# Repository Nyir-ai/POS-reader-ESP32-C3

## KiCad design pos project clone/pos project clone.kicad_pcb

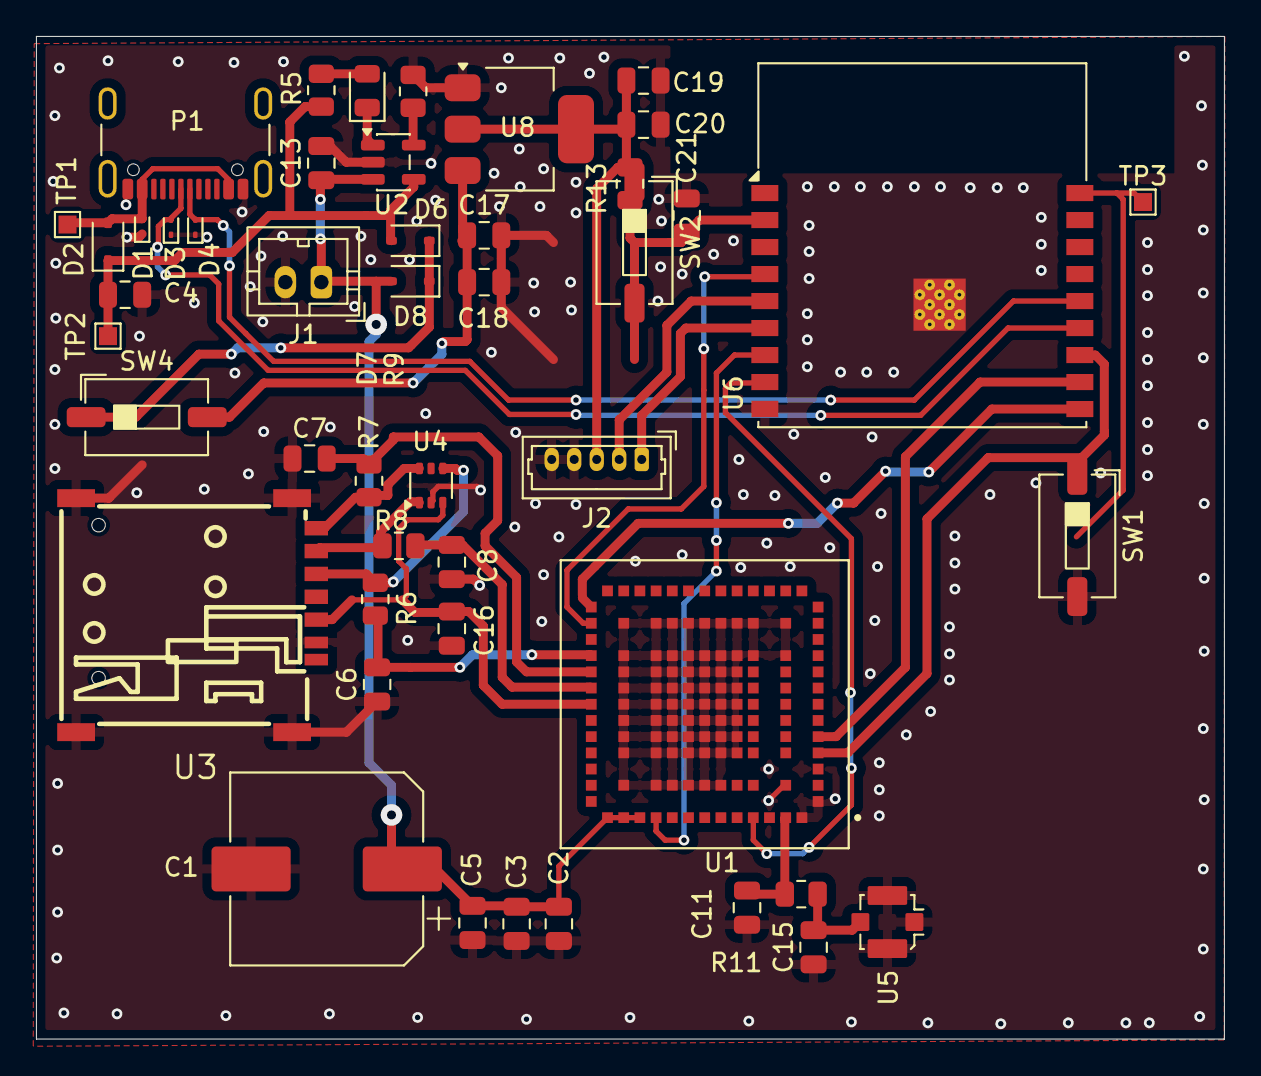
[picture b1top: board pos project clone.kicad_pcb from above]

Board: 2 copper layers, 66.0 x 55.7 mm, 47 parts (0 on the bottom side), 31 nets.

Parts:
C1: 330uF; CP_Elec_10x12.5
C2, C3: 100uF; C_0805_2012Metric
C4, C17, C18: 4.7uF; C_0805_2012Metric
C5: 1uF; C_0805_2012Metric
C6, C7, C8: 33P; C_0805_2012Metric
C11, C15: NC; C_0805_2012Metric
C13, C19, C20, C21: 100nF; C_0805_2012Metric
C16: 104; C_0805_2012Metric
D1, D3, D4: ESD9B3.3ST5G; D_SOD-923
D2: 1N5819WS; D_SOD-323
D6, D8: BAT60A; D_SOD-323
D7: LED; LED_0805_2012Metric
J1: JST_2mm_LiPo; TE_440054-2_1x02_P2.00mm_Vertical
J2: Conn_01x05_Socket; Molex_PicoBlade_53047-0510_1x05_P1.25mm_Vertical
P1: USB_C_Plug_USB2.0; USB_C_Receptacle_GCT_USB4105-xx-A_16P_TopMnt_Horizontal
R5, R9: R_US; R_0805_2012Metric
R6, R7, R8, R11: 22R; R_0805_2012Metric
R13: 10k; R_0805_2012Metric
SW1, SW2: SW_Push; SW_DIP_SPSTx01_Slide_6.7x4.1mm_W6.73mm_P2.54mm_LowProfile_J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
SW4: SW_SPST; SW_DIP_SPSTx01_Slide_6.7x4.1mm_W6.73mm_P2.54mm_LowProfile_J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
TP1: VBUS; TestPoint_Pad_1.0x1.0mm
TP2: VUSB; TestPoint_Pad_1.0x1.0mm
TP3: Test_point; TestPoint_Pad_1.0x1.0mm
U1: LEXI-R10801D-00B; XCVR_LEXI-R10801D-00B
U2: MCP73831-2-OT; SOT-23-5
U3: SMN-303; SIM-SMD_SMN-303
U4: SMF05C; SOT-363_SC-70-6
U5: GSM_ANT; U.FL_Molex_MCRF_73412-0110_Vertical
U6: ESP32-C3-WROOM-02
U8: SGM2212-3.3; SOT-223

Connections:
/ANT_DET: U1.49 (ANT_DET), U6.8 (IO9)
/CLK EN: R7.2, U3.3 (CLK), U4.6 (K5)
/DATA: J2.2 (DATA), U6.5 (IO6)
/DATA EN: R8.2, U3.7 (I/O), U4.1 (K1)
/ESP0/STAT: SW1.1, TP3.1, U6.18 (IO0)
/GPIO18: D3.2 (A2), P1.A7 (D-), U6.13 (IO18)
/GPIO19: D4.2 (A2), P1.A6 (D+), U6.14 (IO19)
/Main ANT: C11.2, R11.1, U1.51 (ANT)
/PWR_ON: U1.27 (~PWR_ON), U6.10 (IO10)
/RESET: U1.28 (~RESET), U6.4 (IO5)
/RST EN: R6.2, U3.2 (RST), U4.4 (K3)
/RXD: U1.4 (~RXD), U6.12 (IO21/TXD)
/SIM1 CLK: C7.2, R7.1, U1.31 (SIM_CLK)
/SIM1 DATA: C8.2, R8.1, U1.32 (SIM_IO)
/SIM1 RST: C6.2, R6.1, U1.30 (SIM_RST)
/SIM1 VCC: C16.1, U1.33 (VSIM), U3.1 (VCC), U4.3 (K2)
/STROBE: J2.1 (STROBE), U6.6 (IO7)
/TXD: U1.5 (~TXD), U6.11 (IO20/RXD)
/VCC_3V3: C19.1, C20.1, J2.3 (VDD), R13.1, U8.2 (VOUT), U8.4 (VOUT)
/V_INT: U1.43 (V_INT), U6.7 (IO8)
GND: C1.2, C2.2, C3.2, C4.2, C5.2, C6.1, C7.1, C8.1, C11.1, C13.2, C15.1, C16.2, C17.2, C18.2, C19.2, C20.2, C21.2, D1.1 (A1), D3.1 (A1), D4.1 (A1), J1.2, J2.4 (GND), J2.5 (CASE), P1.A1 (GND), P1.A12 (GND), P1.B1 (GND), P1.B12 (GND), R9.2, SW1.2, SW2.2, U1.1 (GND_1), U1.3 (GND_1), U1.50 (GND_1), U1.52 (GND_1), U1.53 (GND_1), U1.56 (GND_1), U1.57 (GND_1), U1.58 (GND_1), U1.59 (GND_1), U1.60 (GND_1), U1.61 (GND_1), U1.64 (GND_1), U1.65 (GND_1), U1.66 (GND_1), U1.67 (GND_1), U1.68 (GND_1), U1.69 (GND_1), U1.70 (GND_1), U1.73 (GND_1), U1.74 (GND_1), U1.75 (GND_1), U1.76 (GND_1), U1.77 (GND_1), U1.78 (GND_1), U1.79 (GND_1), U1.82 (GND_1), U1.83 (GND_1), U1.84 (GND_1), U1.85 (GND_1), U1.86 (GND_1), U1.87 (GND_1), U1.88 (GND_1), U1.91 (GND_1), U1.92 (GND_1), U1.93 (GND_1), U1.94 (GND_1), U1.95 (GND_2), U1.96 (GND_2), U1.97 (GND_2), U1.100 (GND_2), U1.101 (GND_2), U1.102 (GND_2), U1.103 (GND_2), U1.104 (GND_2), U1.105 (GND_2), U1.106 (GND_2), U1.109 (GND_2), U1.110 (GND_2), U1.111 (GND_2), U1.112 (GND_2), U1.113 (GND_2), U1.114 (GND_2), U1.115 (GND_2), U1.116 (GND_2), U1.117 (GND_2), U1.118 (GND_2), U1.119 (GND_2), U1.120 (GND_2), U1.121 (GND_2), U1.122 (GND_2), U1.123 (GND_2), U1.124 (GND_2), U1.125 (GND_2), U1.126 (GND_2), U1.127 (GND_2), U1.128 (GND_2), U1.129 (GND_2), U1.130 (GND_2), U1.131 (GND_2), U1.132 (GND_2), U1.133 (GND_2), U2.2 (V_{SS}), U3.5 (GND), U3.8 (EP), U3.9 (EP), U3.10 (EP), U3.11 (EP), U4.2 (A), U5.2, U6.9 (GND), U6.19 (GND), U8.1 (GND/ADJ)
unnamed: C15.2, R11.2, U5.1
unnamed: D1.2 (A2), D2.2 (A), P1.A4 (VBUS), P1.A9 (VBUS), P1.B4 (VBUS), P1.B9 (VBUS), TP1.1
unnamed: D6.1 (K), D8.1 (K), SW4.1 (A)
unnamed: D7.2 (A), R5.2
unnamed: D7.1 (K), U2.1 (STAT)
unnamed: R9.1, U2.5 (PROG)
unnamed: C21.1, R13.2, SW2.1, U6.2 (EN)
VIN: C17.1, C18.1, SW4.2 (B), U8.3 (VIN)
VUSB: C4.1, D2.1 (K), D6.2 (A), R5.1, TP2.1, U2.4 (V_{DD})
V_Batt: C1.1, C2.1, C3.1, C5.1, C13.1, D8.2 (A), J1.1, U1.40 (VCC), U1.41 (VCC), U1.42 (VCC), U2.3 (V_{BAT})

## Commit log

2026-04-09 added schematic and pcb layout
2026-04-10 added switch
